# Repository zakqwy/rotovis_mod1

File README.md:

# rotovis_mod1
2017, Zach Fredin

More Info: https://hackaday.io/project/27829-rotovis-mod1

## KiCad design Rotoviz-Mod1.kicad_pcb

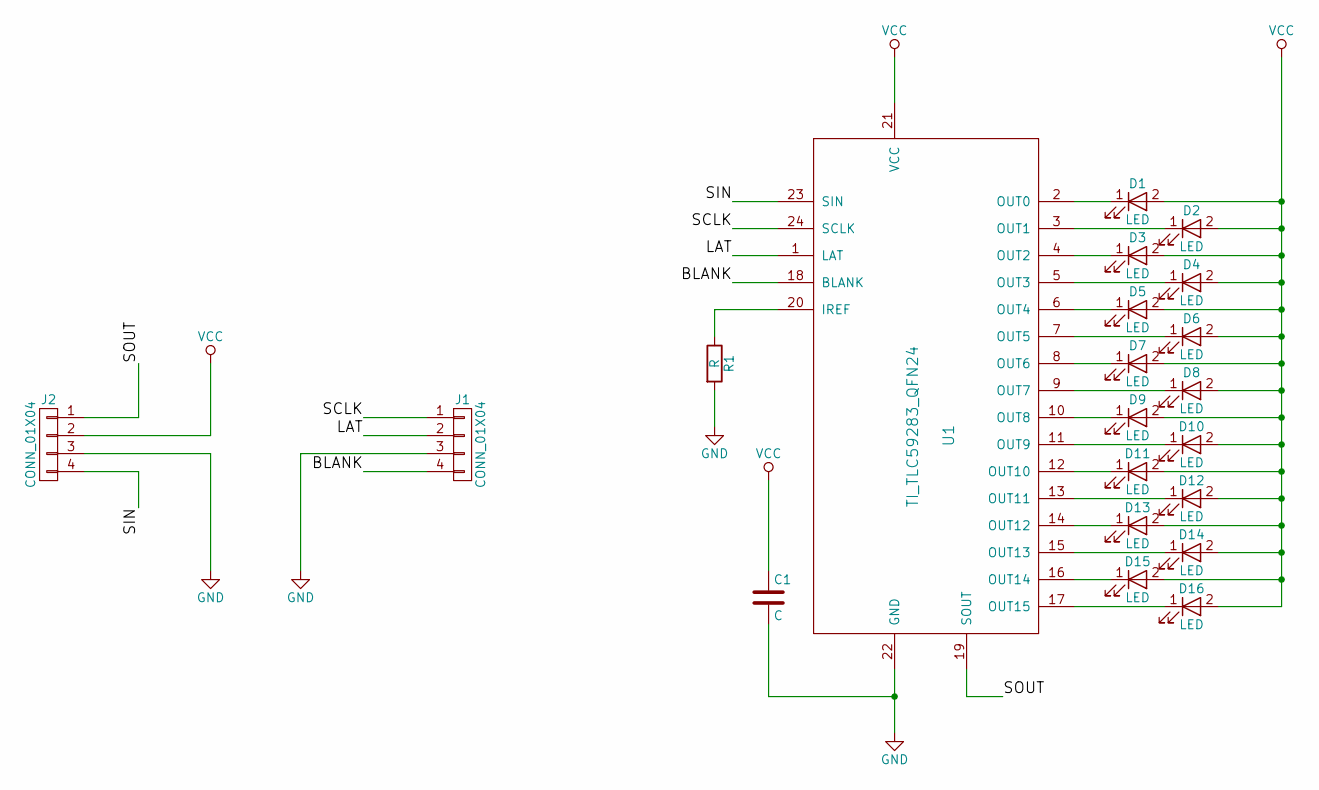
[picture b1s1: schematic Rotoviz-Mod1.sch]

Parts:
C1: C; ZF_SMD_NonPol_0402_cap
D1, D2, D3, D4, D5, D6, D7, D8, D9, D10, D11, D12, D13, D14, D15, D16: LED; ZF_LED_SunLed_0201
J1: CONN_01X04; ZF_CONN_1x4_cast
J2: CONN_01X04; ZF_CONN_1x4_cast-skinny
R1: R; ZF_SMD_NonPol_0402
U1: TI_TLC59283_QFN24; ZF_IC_QFN24-050-short

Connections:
/BLANK: J1.4, U1.18 (BLANK)
/LAT: J1.2, U1.1 (LAT)
/SCLK: J1.1, U1.24 (SCLK)
/SIN: J2.4, U1.23 (SIN)
/SOUT: J2.1, U1.19 (SOUT)
GND: C1.2, J1.3, J2.3, R1.2, U1.22 (GND)
unnamed: D1.1 (K), U1.2 (OUT0)
unnamed: D2.1 (K), U1.3 (OUT1)
unnamed: D3.1 (K), U1.4 (OUT2)
unnamed: D4.1 (K), U1.5 (OUT3)
unnamed: D5.1 (K), U1.6 (OUT4)
unnamed: D6.1 (K), U1.7 (OUT5)
unnamed: D7.1 (K), U1.8 (OUT6)
unnamed: D8.1 (K), U1.9 (OUT7)
unnamed: D9.1 (K), U1.10 (OUT8)
unnamed: D10.1 (K), U1.11 (OUT9)
unnamed: D11.1 (K), U1.12 (OUT10)
unnamed: D12.1 (K), U1.13 (OUT11)
unnamed: D13.1 (K), U1.14 (OUT12)
unnamed: D14.1 (K), U1.15 (OUT13)
unnamed: D15.1 (K), U1.16 (OUT14)
unnamed: D16.1 (K), U1.17 (OUT15)
unnamed: R1.1, U1.20 (IREF)
VCC: C1.1, D1.2 (A), D2.2 (A), D3.2 (A), D4.2 (A), D5.2 (A), D6.2 (A), D7.2 (A), D8.2 (A), D9.2 (A), D10.2 (A), D11.2 (A), D12.2 (A), D13.2 (A), D14.2 (A), D15.2 (A), D16.2 (A), J2.2, U1.21 (VCC)

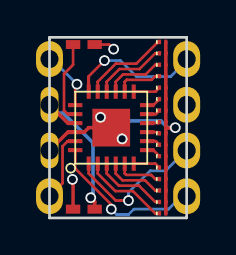
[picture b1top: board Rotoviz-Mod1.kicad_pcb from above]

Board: 2 copper layers, 7.6 x 10.0 mm, 21 parts (0 on the bottom side), 24 nets.

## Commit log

2017-10-22 created README.md. hackaday link not yet live.
2017-10-28 initial upload with tested/good PCB and schematic
